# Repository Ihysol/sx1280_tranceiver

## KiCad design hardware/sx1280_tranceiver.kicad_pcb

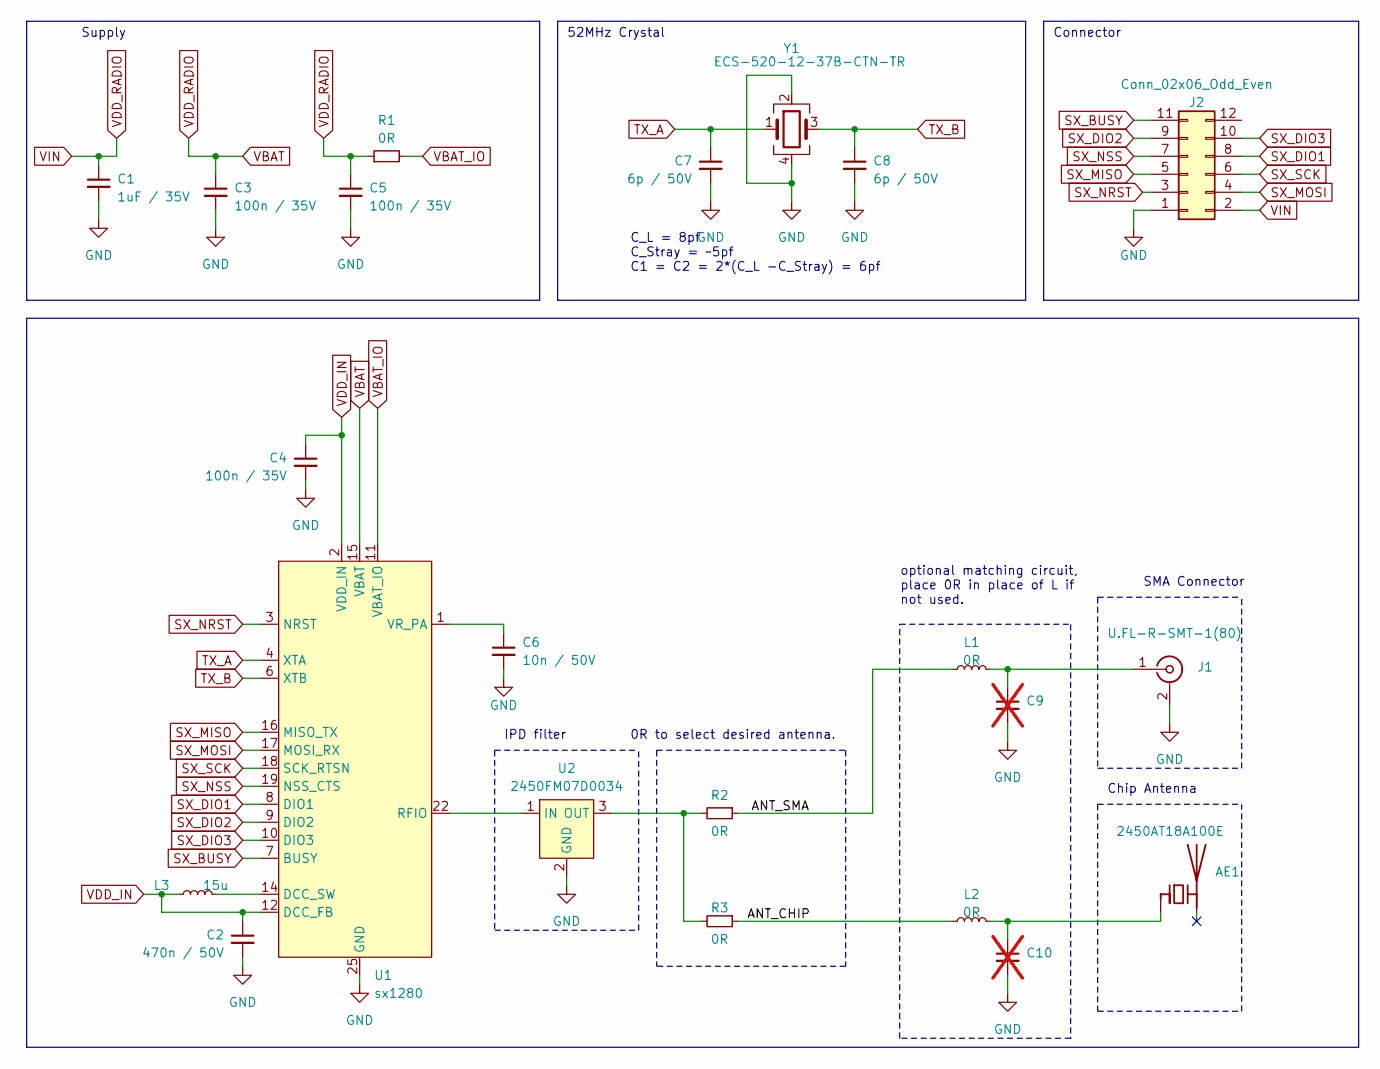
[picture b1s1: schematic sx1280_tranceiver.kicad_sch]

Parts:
AE1: 2450AT18A100E; Johanson_2450AT18x100; LCSC C89334
C1: 1uF / 35V; C_0402_1005Metric; LCSC C307413
C2: 470n / 50V; C_0402_1005Metric; Mouser 81-GRM155R61H474ME1D
C3, C4, C5: 100n / 35V; C_0402_1005Metric; LCSC C187828
C6: 10n / 50V; C_0402_1005Metric; LCSC C60133
C7, C8: 6p / 50V; C_0402_1005Metric; LCSC C1575
C9, C10: C_0402_1005Metric; not fitted
J1: U.FL-R-SMT-1(80); U.FL_Hirose_U.FL-R-SMT-1_Vertical; LCSC C88374
J2: Conn_02x06_Odd_Even; PinHeader_2x06_P2.54mm_Vertical
L1, L2: 0R; L_0402_1005Metric
L3: 15u; L_0805_2012Metric; LCSC C486333
R1: 0R; R_0402_1005Metric
R2, R3: 0R; R_0402_1005Metric; LCSC C17168
U1: sx1280; LCSC C125969
U2: 2450FM07D0034; LCSC C2651081
Y1: ECS-520-12-37B-CTN-TR; Mouser 520-520-12-37B-CTNTR

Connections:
/ANT_CHIP: L2.1, R3.1
/ANT_SMA: L1.1, R2.1
GND: C1.2, C2.2, C3.2, C4.2, C5.2, C6.2, C7.2, C8.2, C9.2, C10.2, J1.2 (Ext), J2.1, U1.5 (GND), U1.13 (GND), U1.20 (GND), U1.21 (GND), U1.23 (GND), U1.24 (GND), U1.25 (GND), U2.2 (GND), U2.4 (GND), Y1.2, Y1.4
unnamed: AE1.1 (FEED), C10.1, L2.2
unnamed: C9.1, J1.1 (In), L1.2
unnamed: L3.2, U1.14 (DCC_SW)
unnamed: U1.22 (RFIO), U2.1 (IN)
unnamed: C6.1, U1.1 (VR_PA)
unnamed: R2.2, R3.2, U2.3 (OUT)
SX_BUSY: J2.11, U1.7 (BUSY)
SX_DIO1: J2.8, U1.8 (DIO1)
SX_DIO2: J2.9, U1.9 (DIO2)
SX_DIO3: J2.10, U1.10 (DIO3)
SX_MISO: J2.5, U1.16 (MISO_TX)
SX_MOSI: J2.4, U1.17 (MOSI_RX)
SX_NRST: J2.3, U1.3 (NRST)
SX_NSS: J2.7, U1.19 (NSS_CTS)
SX_SCK: J2.6, U1.18 (SCK_RTSN)
TX_A: C7.1, U1.4 (XTA), Y1.1
TX_B: C8.1, U1.6 (XTB), Y1.3
VBAT: C1.1, C3.1, C5.1, J2.2, R1.1, U1.15 (VBAT)
VBAT_IO: R1.2, U1.11 (VBAT_IO)
VDD_IN: C2.1, C4.1, L3.1, U1.2 (VDD_IN), U1.12 (DCC_FB)

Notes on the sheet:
0R to select desired antenna.
Connector
C_L = 8pf C_Stray = ~5pf C1 = C2 = 2*(C_L -C_Stray) = 6pf
Chip Antenna
optional matching circuit, place 0R in place of L if not used.
Supply
52MHz Crystal
IPD filter
SMA Connector

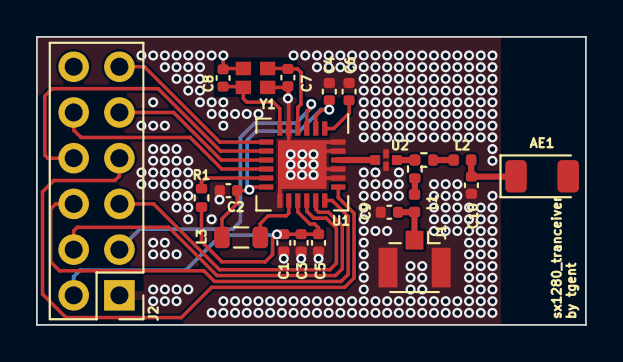
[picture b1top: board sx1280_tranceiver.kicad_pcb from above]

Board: 4 copper layers, 30.5 x 16.0 mm, 22 parts (0 on the bottom side), 23 nets.

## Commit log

2023-09-20 finalized schematic
2023-09-20 moved components in schematic
2023-09-20 layout
2023-09-21 finalized layout
2023-09-21 finalized layout, added part numbers
2023-09-21 added part numbers for bom
2023-10-25 added .gitignore
2023-10-25 added first software implementation
2023-11-16 update to latest codebase
2023-11-16 added error code debugging and sx1280/sx1280_utils.h
2023-11-16 implemented first functions to communicate with the sx1280
2023-11-21 added util files
